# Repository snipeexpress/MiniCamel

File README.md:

<div id="summary" align="center">
</div>

<br/>

<br/>

This is an expansion of the TinyLlama v2 board created by Eivind Bohler. It combines aspects of the ITX llama as well but in a 100mm x 100mm form factor.

- A fully-fledged 486/Pentium-class PC in a small form factor
- Integrated Sound Blaster Pro-compatible audio using the crystal CS4237b sound chip
- Onboard fan controller for optional CPU or case fan support
- Hard drive clicker and system LED on-board with breakout header for installing in a custom case.
- Support for external OPL3 module from the ITX llama.
- Integrated PCM5102 module
- S/PDIF port for digital audio output
- Ethernet port for 10/100 ethernet capability
- Relocated ESP8266 module for use as dial-up modem emulator or wireless network connectivity.
- Add a Raspberry Pi Zero 2 for Roland MT&#8209;32 and General MIDI music
- Open-source hardware schematics, board layout and BIOS - build your own!

## Table of Contents
- [Summary](#summary)
- [Project Goals](#project-goals)
- [What's New In Version 2?](#whats-new-in-version-2)
- [Full system specs](#full-system-specs-revision-21)
- [Building](#building)
  * [Sourcing Parts](#sourcing-parts)
  * [Assembly](#assembly)
  * [Programming the CH559](#programming-the-ch559)
  * [Programming the BIOS](#programming-the-bios)
  * [Installing DOS](#installing-dos)
  * [Programming the CS4237B Firmware](#programming-the-cs4237b-firmware)
- [MT-32 / General MIDI](#mt-32--general-midi)
- [WiFi Connectivity](#wifi-connectivity)
- [Wiki](#wiki)
- [Help](#help)
- [Roadmap](#roadmap)
- [Contributing](#contributing)
- [License](#license)
- [Contact](#contact)
- [Acknowledgements](#acknowledgments)

<br/>

## Project Goals
I'm learning how to build these types of boards and decided to use a project I've built in the past and that I'm familiar with as a starting point.
The biggest goal I have for this project is to learn enough to begin designing my own circuits. In this case, I am relying on circuits that already exist
but my hope is that my next project will be a scratch-built device that doesn't require any use of pre-existing projects.

Both the CH559 and the ESP8266 can be easily re-flashed/programmed in-place.  
Look at [Programming the CH559](#programming-the-ch559) and [Programming the ESP8266][wiki-wifi].

## Full system specs (revision 0.1)
### Hardware
- **86Duino System-on-module**
  * Vortex86EX CPU running at 60-500 MHz
  * 16 KB L1 cache (can be disabled)
  * 128 KB L2 cache
  * 128 MB DDR3 RAM
  * 8 MB programmable flash ROM
- **Vortex86VGA module running off a x1 PCI-e lane**
  * Maximum resolution: 1024x768, 60 Hz
  * 4 MB SRAM
  * [Alternative graphics cards][wiki-alternative-gpus]
- **Crystal CS4237B all-in-one audio chip**
- **12mm PC-speaker**
- **12mm HDD clicker speaker**
- **CR1220 battery for persistent real-time clock**
- **Power and reset buttons**
- **Connectivity**
  * USB-C for power
  * 2 x USB Type-A connectors for HID-compliant keyboard and mice
  * 2 x USB Type-A connectors for storage devices (USB 2.0)
  * MicroSD slot for storage
  * DE-9 RS232 serial port (COM1)
  * 1x RJ45 10/100 Ethernet port
  * Modem or Ethernet/SLIP over WiFi (COM2)
  * Internal fan pin-header (5V only)
  * 3.5mm line-out audio jack
  * S/PDIF jack for digital line out
- **mt32-pi subsystem**
  * 40-pin connector for a Raspberry Pi Zero 2
  * Integrated PCM5102 I²S DAC module
  * Button for toggling between MT32 / General MIDI mode
  * Button for switching between audio ROMs / soundbanks
  * 4-pin I²C connector for an OLED display

### Software
- **[Custom Coreboot/SeaBIOS ROM][bios]**
- **MS-DOS / FreeDOS**

## Building
### Sourcing Parts
I will post the BOM after I complete the initial test build to make sure everything is correct.

#### For MT-32/MIDI - optional
- Raspberry Pi Zero 2 W with a microSD card
- An [mt32-pi compatible OLED display][mt32-pi-oled], optional but nice

### Programming the CH559
1. Download the latest firmware binary from this repo, in the `hidman-binary` folder. Alternatively, get the latest source code from the [official repo][hidman] and compile it yourself.
2. Download and install `WCHISPTool_Setup.exe` from [WCH's website][wch]. Unfortunately, this tool only supports Windows. If you're on macOS or Linux, maybe try using virtualization software, or even another computer.
3. Open the `WCHISPTool_CH54x-55x` application.
4. Make sure the MiniCamel is powered off.
5. **Remove** the jumper from the "HID_POWER" pin header on the PCB (to ensure that the computer doesn't backpower the MiniCamel).
6. Connect a USB cable (type A to type A) between one of the HID USB ports on the MiniCamel and the Windows computer.
7. Press and hold the "PRG" button on the bottom side of the MiniCamel until the CH559 device pops up in the WCHISPTool.
8. Select the firmware binary file under _Download File -> Object File1_.
9. Click the "Download" button. Hopefully you'll get a success message in the log section on the right side of the program window.
10. Disconnect the USB cable.
11. **Add** the jumper to the "HID_POWER" pin header on the PCB.
12. Connect a keyboard to one of the HID USB ports. You should be good to go!

### Programming the BIOS
When purchasing the SOM-128-EX module from DMP, its ROM chip comes preinstalled with an Arduino-like bootloader which isn't what we want. Also, the  "crossbar" is configured for using the module with the 86Duino Zero/One boards - meaning its default pin layout is completely different from what we need for the MiniCamel.

Follow these steps to flash the ROM with the MiniCamel BIOS for the first time:
1. Find a USB flash drive, must be minimum 32 MB in size (shouldn't be a problem these days). Note that not all USB drives are bootable. Use a well-known bootable drive. _NB: You have to use a USB stick for this, an SD card won't work since the crossbar is configured to use different pins on the SOM for SD traffic._
2. Do a block-level transfer of the `INITBIOS.IMG` from this repo to the USB drive. Use [Balena Etcher][balena-etcher], or the command line if you know what you're doing (macOS example):
```
$ diskutil list
(Find your USB drive, eg. /dev/disk2)
$ diskutil unmountDisk /dev/disk2
$ sudo dd if=INITBIOS.IMG of=/dev/rdisk2 bs=1m
```
3. Insert the USB flash drive into the MiniCamel and turn it on. It'll hopefully boot into MS-DOS. Then, to flash the ROM:
```
C:\>anybios w initbios.rom
```
...and reboot.  

For subsequent BIOS updates, you can use the ROM's built-in virtual floppy drive available from the boot menu (press F12).  
When booted from this you'll only need a regular USB stick (formatted as FAT16/FAT32) containing the new BIOS file.

### Installing MS-DOS
_A note on selecting the DOS type:  
I've gone with MS-DOS 6.22 for maximum compatibility.  
If you prefer FreeDOS (or another DOS variant), prepare a bootable USB installer disk and use that instead of the built-in virtual floppy._
1. Pick a bootable USB drive or Micro SD card to use as the boot drive - for MS-DOS 6.22 you'll be limited to FAT16 and 2 GB per partition (though you can have several). For FreeDOS with FAT32 you can go all the way up to 2 TB.
2. Insert it, turn on the system, press F12 to bring up the boot menu, and select the virtual floppy drive.
3. Use `fdisk` from the command prompt to partition the SD/USB drive and set it to be `Active`.
4. Restart and again select to boot from the virtual floppy.  
Use `format c: /s /u` to format the drive and copy over system files. Finally use `fdisk /mbr` to make sure the Master Boot Record is correct and the drive should be bootable.
5. Copy over the `DOS` folder from A: to C:.  
You can either do this manually and create `CONFIG.SYS` and `AUTOEXEC.BAT` files to your liking, or more conveniently, just run the `SETUP.BAT` script that'll do this for you. The provided config files lets you choose from a clean boot or a QEMM-based one with XMS, EMS and 631 kB of free conventional memory.

### Programming the CS4237B Firmware
1. Copy the `CS4237B` and `UNISOUND` folders from this GitHub repo over to your SD/USB boot drive and start the system.
2. To program the firmware, run the `RESOURCE.EXE` command below and check that you get the same output:
```
C:\>cd cs4237b
C:\CS4237B>resource /f=0x120 /r=cs4237b.asm /e

Reading data from CS4237B.ASM
Length = 292    Programming EEPROM Block: 1 2    EEPROM programmed

Verifying EEPROM:
Verifying CS4237B.ASM against EEPROM . . .      Verified OKAY
```
3. Make sure the correct `BLASTER` environment variable is set and `UNISOUND.COM` command is called from `AUTOEXEC.BAT`. Note that the 8-bit DMA channel is **1** and the IRQ is **7**:
```
SET BLASTER=A220 I7 D1 P330 T4
C:\UNISOUND\UNISOUND.EXE /V60 /VW60 /VF60 /VL60 /VP60 /VC0 /VM0
```
4. Reboot the system, and you should get the following output:
```
Universal ISA PnP Sound Card Driver for DOS v0.76f. (c) JazeFox 2019-21
-----------------------------------------------------------------------
PnP card found: [CSC7537] CS4237B
BLASTER environment var found! Loading settings...
ADD:220 WSS:534 OPL:388 IRQ:7 DMA:1/1 MPU:330/I9 CTR:120 JOY:200
Initialization done.
Crystal Mixer [VOL:85 WAV:80 FM:80 LIN:0 CD:0 MIC:0]
```
5. Feel free to experiment with the different volume levels, look at the `C:\UNISOUND\UNISOUND.TXT` file for further guidance.
6. Fire up a few games to test that Adlib, SoundBlaster FM and digital sound effects are working properly.

## MT-32 / General MIDI
If you've installed [mt32-pi][mt32-pi] on a Raspberry Pi Zero 2 and connected it to the TinyLlama, it should be ready to go using IO port 330. Use the third button from the left (labeled "SYNTH_SW" on the PCB) to switch between MT-32 and General MIDI mode.  
If you want to play old games that require "MPU-401 Intelligent Mode" (Sierra games, Monkey Island 1, etc), try running [SoftMPU][softmpu]:
```
C:\SOFTMPU\>softmpu /mpu:330 /sb:220 /irq:7
```
If you want to hook up an I²C OLED display to the mt32-pi, there's a pin header on the MiniCamel labeled "I2C_OLED". The order of the pins from 1 to 4 is: GND, VCC, SCL, SDA with pin 1 being the one closest to the 3.5mm audio jack.

## WiFi Connectivity
There's a [section][wiki-wifi] in the wiki dedicated to this, take a look.

## Wiki
For an in-depth discussion of the various components, installation, configuration, etc, take a look at the [wiki][wiki].

## Help
This project is indended for people with a fair bit of hardware- and DOS knowledge. If you have questions or need help, please look at the [wiki][wiki] and [FAQ][wiki-faq] section first.

## License
[GNU General Public License v3.0](LICENSE)

## Acknowledgements

Many thanks to

- [Eivind Bohler] for creating the initial project, helping me troubleshoot my ITX llama and being a HUGE inspiration.
- [Rasteri][rasteri-videos] for creating the WeeCee and Wee86 that got me interested in going down this rabbit hole.
- [The Vogons forum][vogons] for being a great resource and always providing help when needed.
- [86Duino / DMP][86duino] for making a great and affordable system-on-module. (I concur with Eivind on this!)

[tinyllama1]: https://github.com/eivindbohler/tinyllama
[hidman]: https://github.com/rasteri/HIDman
[wiki-alternative-gpus]: https://github.com/eivindbohler/tinyllama2/wiki/alternative-gpus
[bios]: https://github.com/eivindbohler/tinyllama2-bios

[wiki]: https://github.com/eivindbohler/tinyllama2/wiki
[wiki-assembly]: https://github.com/eivindbohler/tinyllama2/wiki/assembly
[wiki-bom]: https://github.com/eivindbohler/tinyllama2/wiki/bom
[wiki-faq]: https://github.com/eivindbohler/tinyllama2/wiki/faq
[wiki-wifi]: https://github.com/eivindbohler/tinyllama2/wiki/wifi-connectivity

[balena-etcher]: https://www.balena.io/etcher
[mt32-pi-oled]: https://github.com/dwhinham/mt32-pi/wiki/LCD-and-OLED-display
[wch]: http://www.wch-ic.com/products/CH559.html

[issues]: https://github.com/eivindbohler/tinyllama2/issues

[rasteri-videos]: https://www.youtube.com/user/TheRasteri/videos
[vogons]: https://www.vogons.org
[86duino]: https://www.86duino.com
[mt32-pi]: https://github.com/dwhinham/mt32-pi
[softmpu]: http://bjt42.github.io/softmpu

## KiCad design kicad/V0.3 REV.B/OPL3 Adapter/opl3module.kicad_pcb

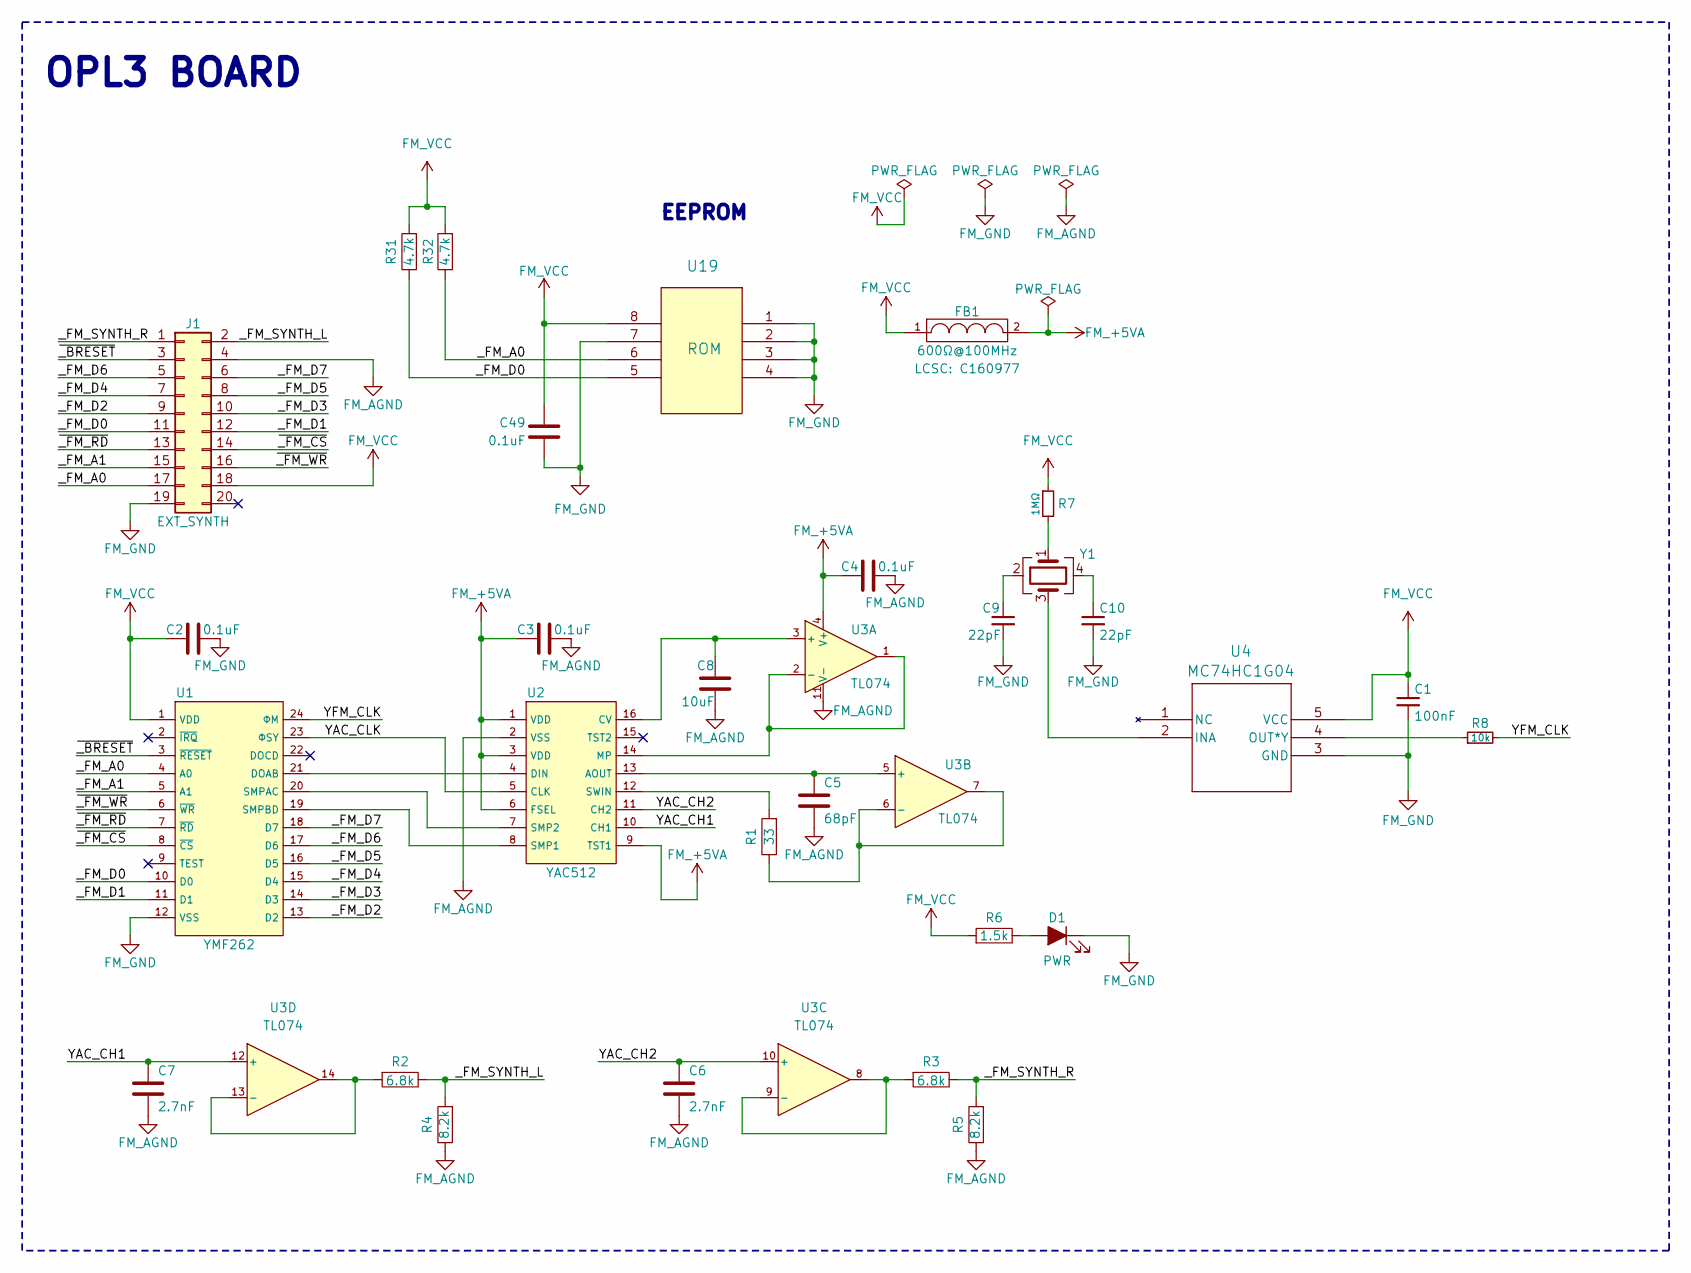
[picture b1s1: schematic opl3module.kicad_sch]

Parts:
C1: 100nF; C_0402_1005Metric
C2, C3, C4, C49: 0.1uF; C_0402_1005Metric_no_outline
C5: 68pF; C_0402_1005Metric_no_outline
C6, C7: 2.7nF; C_0603_1608Metric_no_outline
C8: 10uF; C_0603_1608Metric_no_outline
C9, C10: 22pF; C_0402_1005Metric
D1: PWR; D_0603_1608Metric; LCSC C130723
FB1: 600Ω@100MHz; R_0402_1005Metric_no_outline; LCSC C160977
J1: EXT_SYNTH; P_CONN_02X10
R1: 33; R_0402_1005Metric_no_outline
R2, R3: 6.8k; R_0402_1005Metric_no_outline
R4, R5: 8.2k; R_0402_1005Metric_no_outline
R6: 1.5k; R_0603_1608Metric_no_outline; LCSC C25117
R7: 1MΩ; R_0603_1608Metric
R8: 10k; R_0603_1608Metric
R31, R32: 4.7k; R_0402_1005Metric_no_outline
U1: YMF262; SOP-24_7.5x15.4mm_P1.27mm
U2: YAC512; SOP-16_4.4x10.4mm_P1.27mm
U3: TL074; SOIC-14_3.9x8.7mm_P1.27mm
U4: MC74HC1G04; SC70-5_ONS
U19: ROM; SOIC8-N_MC_MCH
Y1: Crystal_GND24; Crystal_SMD_5032-4Pin_5.0x3.2mm

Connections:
/YAC_CH1: C7.1, U2.10 (CH1), U3.12 (+)
/YAC_CH2: C6.1, U2.11 (CH2), U3.10 (+)
/YAC_CLK: U1.23 (ΦSY), U2.5 (CLK)
/YFM_CLK: R8.2, U1.24 (ΦM)
/_FM_A0: J1.17, R32.1, U1.4 (A0), U19.6
/_FM_A1: J1.15, U1.5 (A1)
/_FM_D0: J1.11, R31.1, U1.10 (D0), U19.5
/_FM_D1: J1.12, U1.11 (D1)
/_FM_D2: J1.9, U1.13 (D2)
/_FM_D3: J1.10, U1.14 (D3)
/_FM_D4: J1.7, U1.15 (D4)
/_FM_D5: J1.8, U1.16 (D5)
/_FM_D6: J1.5, U1.17 (D6)
/_FM_D7: J1.6, U1.18 (D7)
/_FM_SYNTH_L: J1.2, R2.1, R4.2
/_FM_SYNTH_R: J1.1, R3.1, R5.2
/~_BRESET: J1.3, U1.3 (~RESET)
/~_FM_CS: J1.14, U1.8 (~CS)
/~_FM_RD: J1.13, U1.7 (~RD)
/~_FM_WR: J1.16, U1.6 (~WR)
FM_+5VA: C3.2, C4.2, FB1.2, U2.1 (VDD), U2.3 (VDD), U2.6 (FSEL), U2.9 (TST1), U3.4 (V+)
FM_AGND: C3.1, C4.1, C5.2, C6.2, C7.2, C8.1, J1.4, R4.1, R5.1, U2.2 (VSS), U3.11 (V-)
FM_GND: C1.2, C2.1, C9.2, C10.2, C49.2, D1.1 (K), J1.19, U1.12 (VSS), U4.3 (GND), U19.1, U19.2, U19.3, U19.4, U19.7
FM_VCC: C1.1, C2.2, C49.1, FB1.1, J1.18, R6.2, R7.1, R31.2, R32.2, U1.1 (VDD), U4.5 (VCC), U19.8
unnamed: C9.1, Y1.2
unnamed: C10.1, Y1.4
unnamed: D1.2 (A), R6.1
unnamed: R7.2, Y1.1
unnamed: U1.21 (DOAB), U2.4 (DIN)
unnamed: U1.20 (SMPAC), U2.7 (SMP2)
unnamed: U1.19 (SMPBD), U2.8 (SMP1)
unnamed: C5.1, U2.13 (AOUT), U3.5 (+)
unnamed: C8.2, U2.16 (CV), U3.3 (+)
unnamed: U2.14 (MP), U3.1, U3.2 (-)
unnamed: R1.2, U2.12 (SWIN)
unnamed: R1.1, U3.6 (-), U3.7
unnamed: R3.2, U3.8, U3.9 (-)
unnamed: R2.2, U3.13 (-), U3.14
unnamed: U4.2 (INA), Y1.3
unnamed: R8.1, U4.4 (OUT*Y)

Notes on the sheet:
OPL3 BOARD
EEPROM

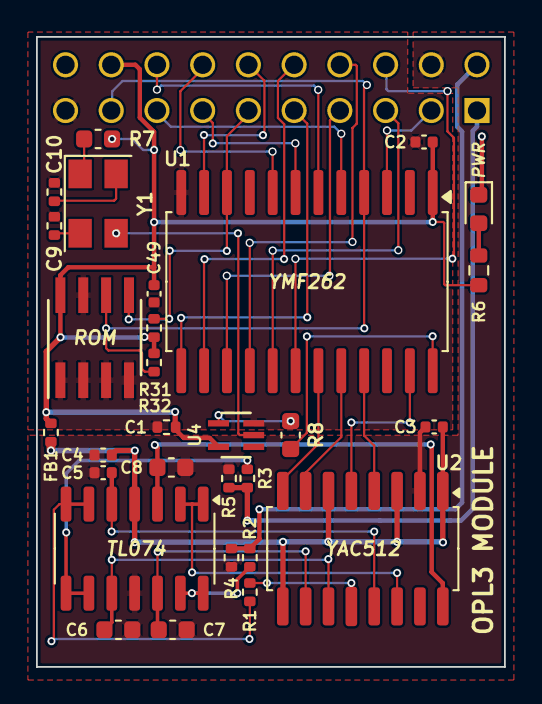
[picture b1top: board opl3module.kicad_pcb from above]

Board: 4 copper layers, 26.0 x 35.0 mm, 30 parts (1 on the bottom side), 40 nets.

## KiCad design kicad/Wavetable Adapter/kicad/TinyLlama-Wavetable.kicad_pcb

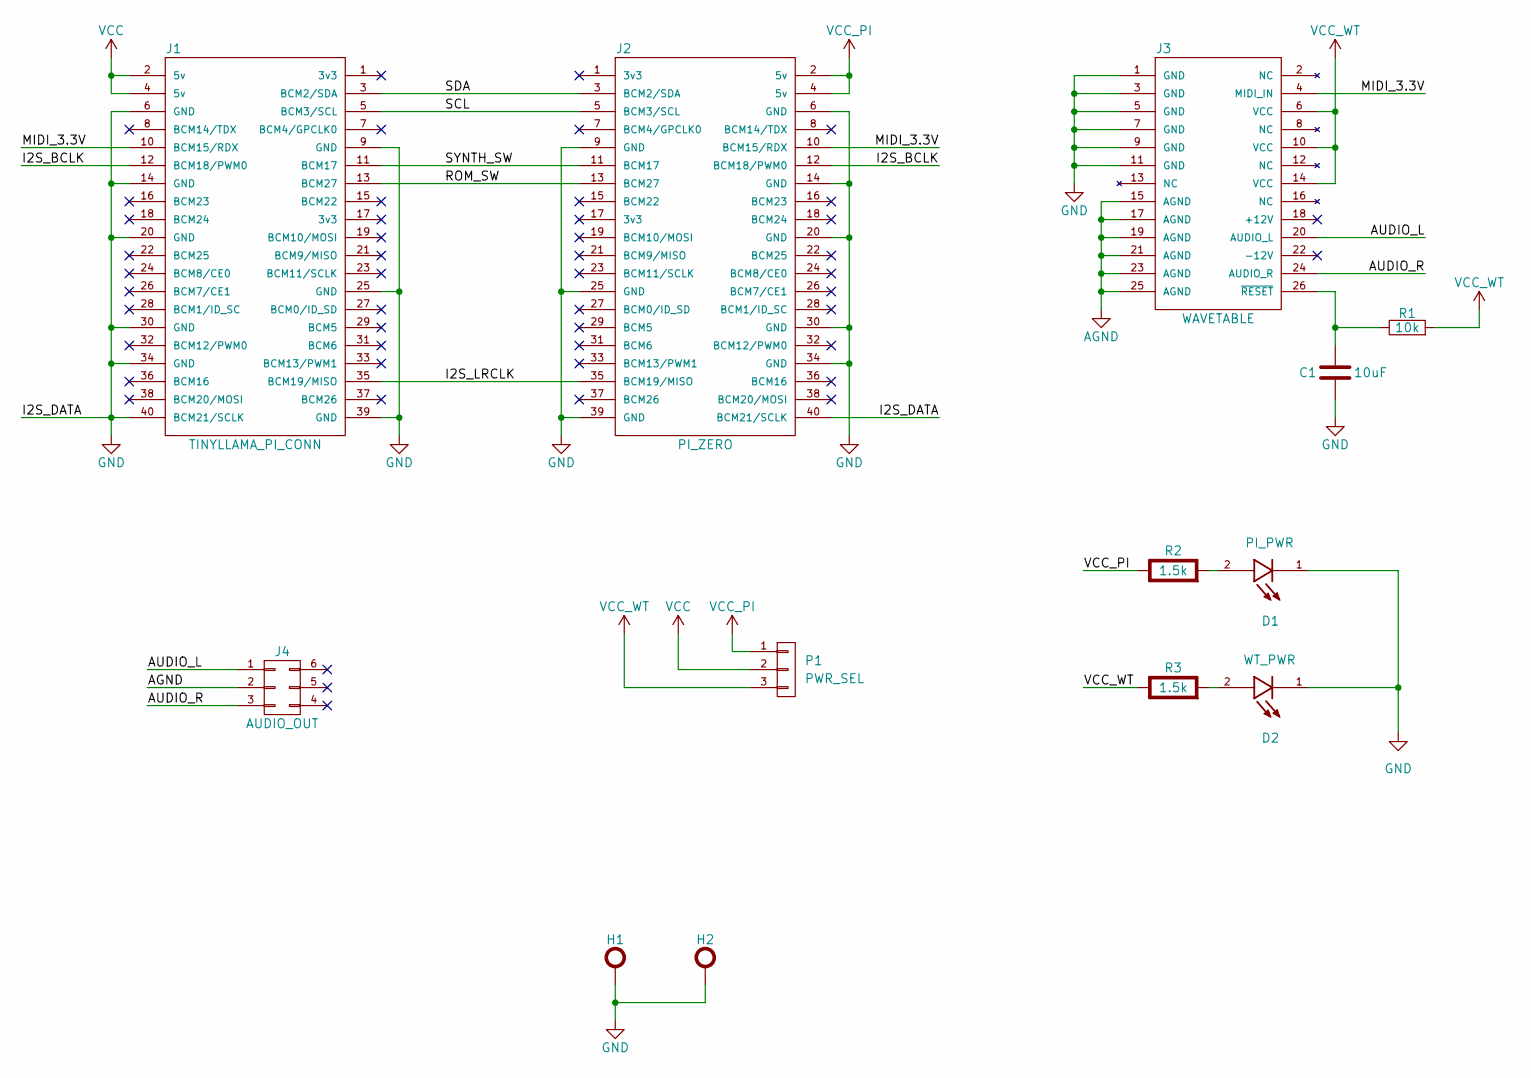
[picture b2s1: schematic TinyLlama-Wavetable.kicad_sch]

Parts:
C1: 10uF; C_0603_1608Metric
D1: PI_PWR; D_0805_2012Metric; PARTREV D; LCSC C130723
D2: WT_PWR; D_0805_2012Metric; PARTREV D; LCSC C130723
H1, H2: H_HOLE; H_440_HOLE
J1: TINYLLAMA_PI_CONN; J_CONN_RPI_MIRRORED_SMD
J2: PI_ZERO; J_CONN_RPI_SMD
J3: WAVETABLE; J_CONN_WAVETABLE
J4: AUDIO_OUT; P_CONN_02X03_SMD
P1: PWR_SEL; PinHeader_1x03_P2.54mm_Horizontal
R1: 10k; R_0603_1608Metric
R2, R3: 1.5k; R_0603_1608Metric; Rating W

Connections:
/AUDIO_L: J3.20 (AUDIO_L), J4.1
/AUDIO_R: J3.24 (AUDIO_R), J4.3
/I2S_BCLK: J1.12 (BCM18/PWM0), J2.12 (BCM18/PWM0)
/I2S_LRCLK: J1.35 (BCM19/MISO), J2.35 (BCM19/MISO)
/MIDI_3.3V: J1.10 (BCM15/RDX), J2.10 (BCM15/RDX), J3.4 (MIDI_IN)
/ROM_SW: J1.13 (BCM27), J2.13 (BCM27)
/SCL: J1.5 (BCM3/SCL), J2.5 (BCM3/SCL)
/SDA: J1.3 (BCM2/SDA), J2.3 (BCM2/SDA)
/SYNTH_SW: J1.11 (BCM17), J2.11 (BCM17)
AGND: J3.15 (AGND), J3.17 (AGND), J3.19 (AGND), J3.21 (AGND), J3.23 (AGND), J3.25 (AGND), J4.2
GND: C1.2, D1.1, D2.1, H1.1, H2.1, J1.6 (GND), J1.9 (GND), J1.14 (GND), J1.20 (GND), J1.25 (GND), J1.30 (GND), J1.34 (GND), J1.39 (GND), J1.40 (BCM21/SCLK), J2.6 (GND), J2.9 (GND), J2.14 (GND), J2.20 (GND), J2.25 (GND), J2.30 (GND), J2.34 (GND), J2.39 (GND), J2.40 (BCM21/SCLK), J3.1 (GND), J3.3 (GND), J3.5 (GND), J3.7 (GND), J3.9 (GND), J3.11 (GND)
unnamed: C1.1, J3.26 (~RESET), R1.1
unnamed: D1.2, R2.2 (-)
unnamed: D2.2, R3.2 (-)
VCC: J1.2 (5v), J1.4 (5v), P1.2
VCC_PI: J2.2 (5v), J2.4 (5v), P1.1, R2.1 (+)
VCC_WT: J3.6 (VCC), J3.10 (VCC), J3.14 (VCC), P1.3, R1.2, R3.1 (+)

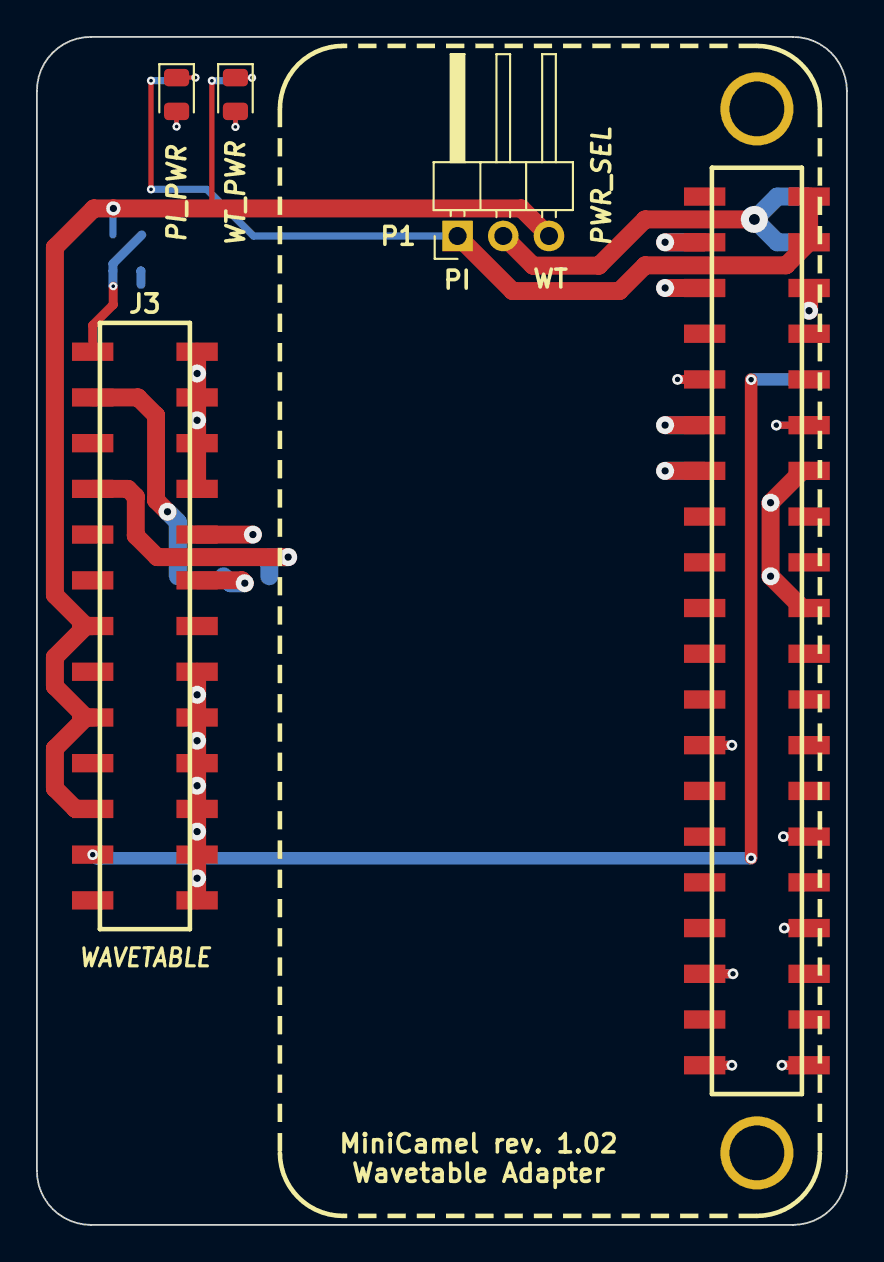
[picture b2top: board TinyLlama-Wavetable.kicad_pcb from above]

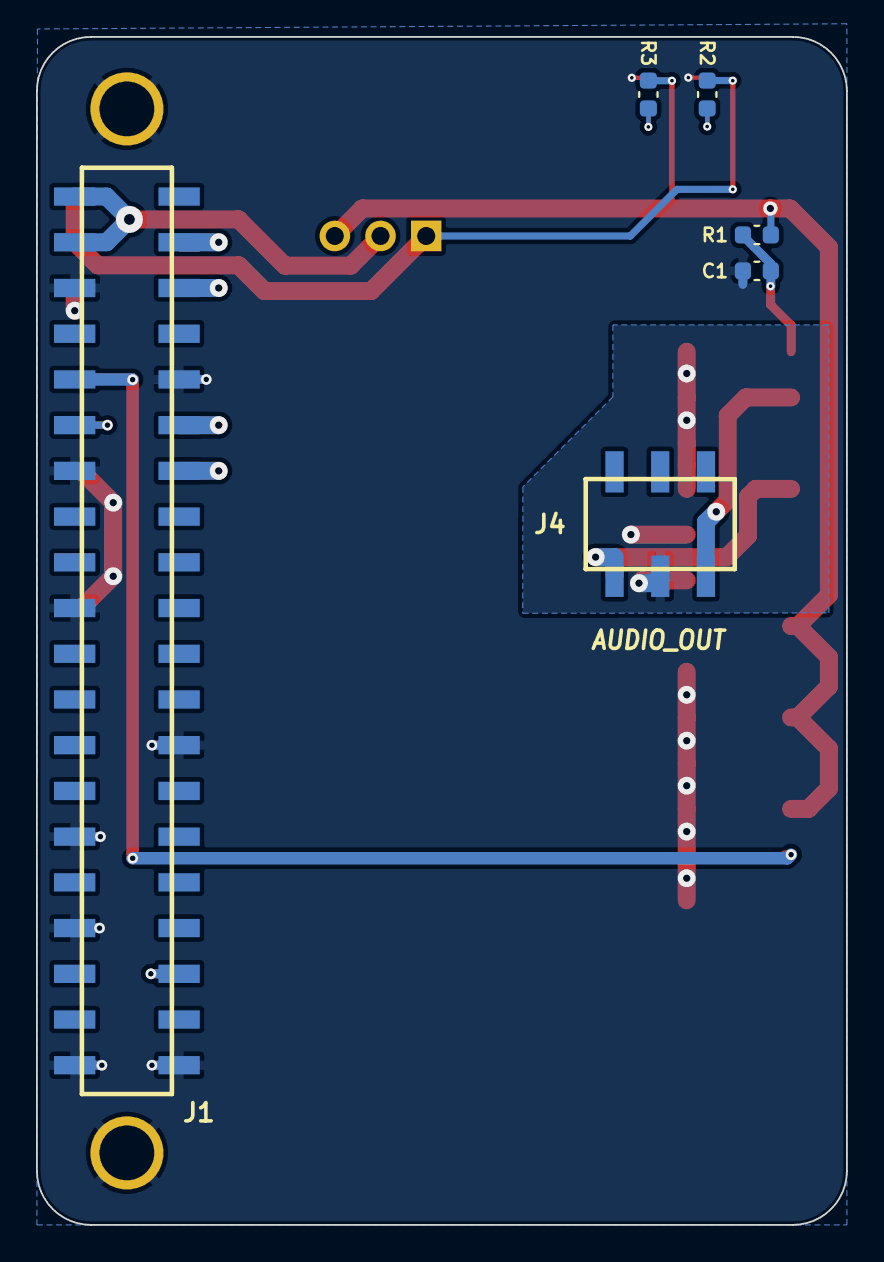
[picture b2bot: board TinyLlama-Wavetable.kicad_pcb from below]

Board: 2 copper layers, 45.0 x 66.0 mm, 13 parts (6 on the bottom side), 17 nets.

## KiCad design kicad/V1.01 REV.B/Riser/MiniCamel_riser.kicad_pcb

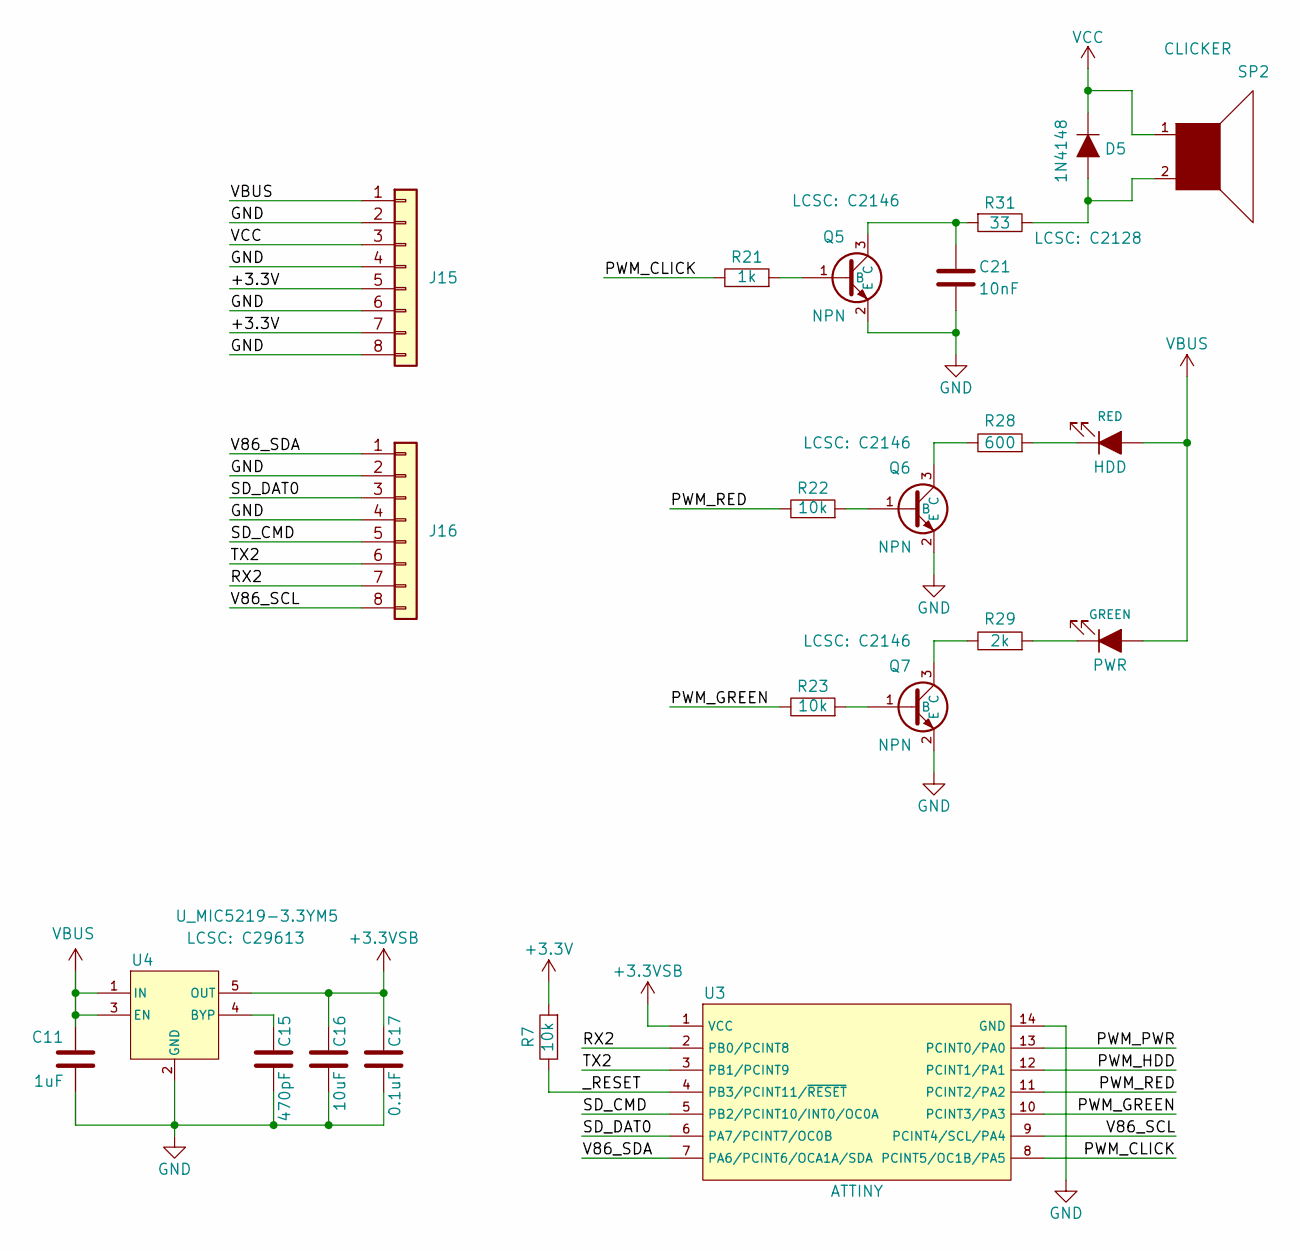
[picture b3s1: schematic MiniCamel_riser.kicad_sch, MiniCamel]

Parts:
C11: 1uF; C_0603_1608Metric; LCSC C207017
C15: 470pF; C_0603_1608Metric; LCSC C207017
C16: 10uF; C_0603_1608Metric; LCSC C207017
C17: 0.1uF; C_0603_1608Metric; LCSC C207017
C21: 10nF; C_0603_1608Metric; LCSC C207017
D5: 1N4148; D_SOD-323F; LCSC C2128
D6: PWR; LED_LTST-S220KSKT; PARTREV D; LCSC C130723
D7: HDD; LED_LTST-S220KSKT; PARTREV D; LCSC C130723
J15, J16: Conn_01x06; PinHeader_1x08_P2.54mm_Vertical_no_outline
Q5, Q6, Q7: NPN; Q_BJT_SOT-23-3; LCSC C2146
R7, R22, R23: 10k; R_0603_1608Metric; LCSC C207017
R21: 1k; R_0603_1608Metric; LCSC C207017
R28: 600; R_0603_1608Metric; LCSC C207017
R29: 2k; R_0603_1608Metric; LCSC C207017
R31: 33; R_0603_1608Metric; LCSC C207017
SP2: CLICKER; XDCR_SMT-0927-S-12-R; PARTREV 1/19/2017; LCSC C252917
U3: ATTINY; SOIC-14_3.9x8.7mm_P1.27mm
U4: U_MIC5219-3.3YM5; U_SOT-23-5; LCSC C29613

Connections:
+3.3V: J15.5, J15.7, R7.2
+3.3VSB: C16.1, C17.2, U3.1 (VCC), U4.5 (OUT)
/PWM_CLICK: R21.1, U3.8 (PCINT5/OC1B/PA5)
/PWM_GREEN: R23.1, U3.10 (PCINT3/PA3)
/PWM_HDD: U3.12 (PCINT1/PA1)
/PWM_PWR: U3.13 (PCINT0/PA0)
/PWM_RED: R22.1, U3.11 (PCINT2/PA2)
/RX2: J16.7, U3.2 (PB0/PCINT8)
/SD_CMD: J16.5, U3.5 (PB2/PCINT10/INT0/OC0A)
/SD_DAT0: J16.3, U3.6 (PA7/PCINT7/OC0B)
/TX2: J16.6, U3.3 (PB1/PCINT9)
/V86_SCL: J16.8, U3.9 (PCINT4/SCL/PA4)
/V86_SDA: J16.1, U3.7 (PA6/PCINT6/OCA1A/SDA)
/_RESET: R7.1, U3.4 (PB3/PCINT11/~RESET)
GND: C11.2, C15.2, C16.2, C17.1, C21.2, J15.2, J15.4, J15.6, J15.8, J16.2, J16.4, Q5.2 (E), Q6.2 (E), Q7.2 (E), U3.14 (GND), U4.2 (GND)
unnamed: D5.2 (A), R31.1, SP2.2
unnamed: D6.1 (K), R29.2
unnamed: D7.1 (K), R28.2
unnamed: Q5.1 (B), R21.2
unnamed: C21.1, Q5.3 (C), R31.2
unnamed: Q6.1 (B), R22.2
unnamed: Q6.3 (C), R28.1
unnamed: Q7.1 (B), R23.2
unnamed: Q7.3 (C), R29.1
unnamed: C15.1, U4.4 (BYP)
VBUS: C11.1, D6.2 (A), D7.2 (A), J15.1, U4.1 (IN), U4.3 (EN)
VCC: D5.1 (K), J15.3, SP2.1

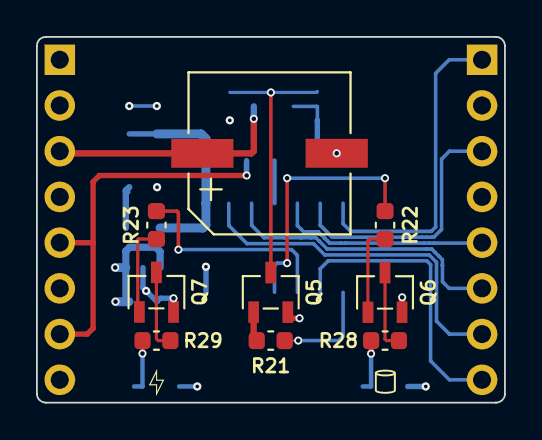
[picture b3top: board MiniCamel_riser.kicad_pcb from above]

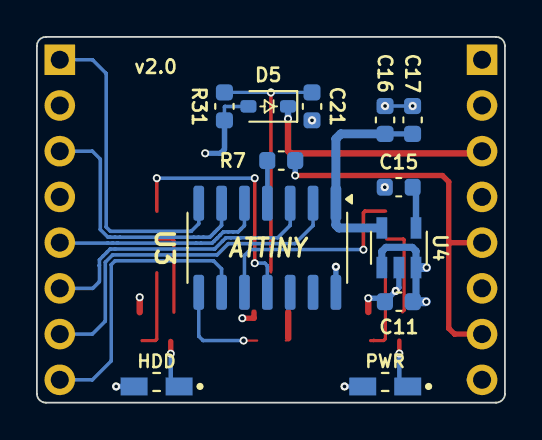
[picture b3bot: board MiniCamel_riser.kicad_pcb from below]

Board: 4 copper layers, 26.0 x 20.3 mm, 23 parts (14 on the bottom side), 25 nets.
